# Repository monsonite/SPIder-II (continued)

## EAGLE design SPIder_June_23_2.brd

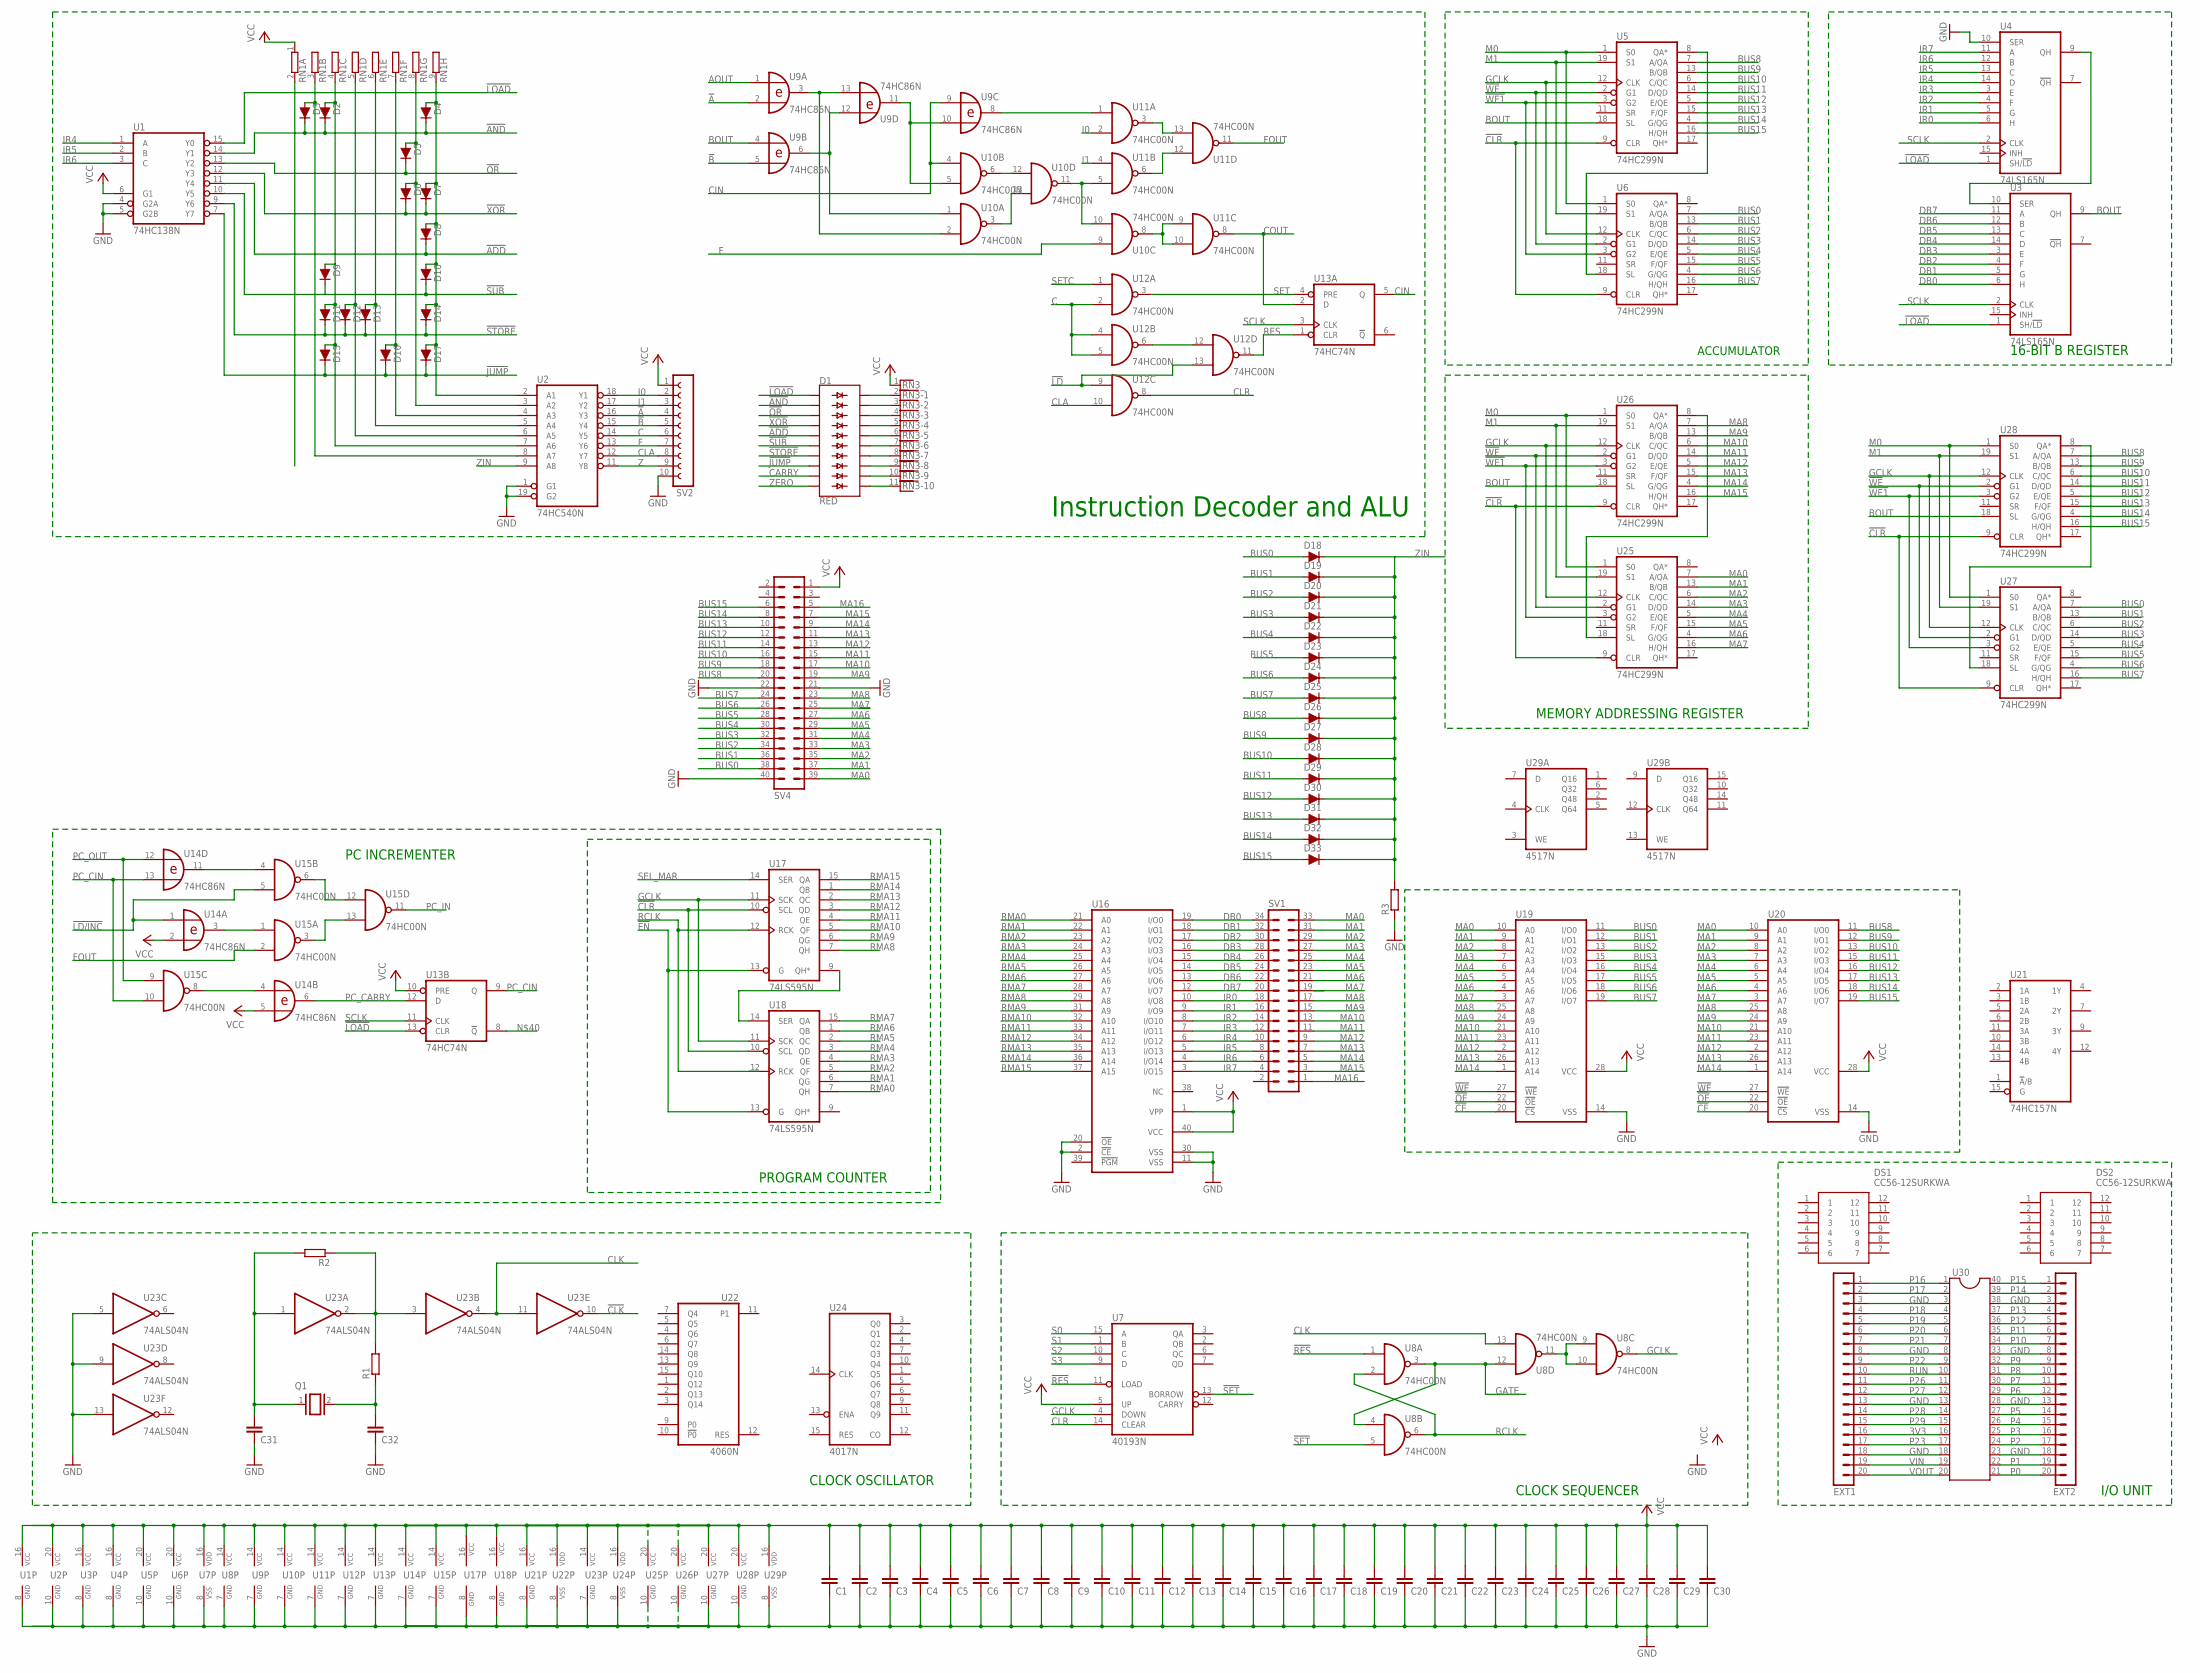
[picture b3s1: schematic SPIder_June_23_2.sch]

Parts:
C1, C2, C3, C4, C5, C6, C7, C8, C9, C10, C11, C12, C13, C14, C15, C16, C17, C18, C19, C20, C21, C22, C23, C24, C25, C26, C27, C28, C29, C30, C31, C32: C-EU025-024X044; C025-024X044
D1: RED; LED_BARGRAPH_10
D2, D3, D4, D5, D6, D7, D8, D9, D10, D11, D12, D13, D14, D15, D16, D17, D19, D20, D21, D22, D23, D24, D25, D26, D27, D28, D29, D30, D31, D32, D33: 200mA/100V/1V; DIODE-1N4148
D18: 200mA/100V/1V; DIODE-1N4148-KIT
DS1, DS2: CC56-12SURKWA; DIPS1524W75P254L5030H810Q12N
EXT1, EXT2: MA20-1
Q1: XTAL/S; QS
R1, R2, R3: R-EU_0204/5; 0204/5
RN1: GE08R; SIL9
RN3: RNX10; RN-11
SV1: MA17-2
SV2: FE10-1; FE10
SV4: MA20-2
U1: 74HC138N; DIL16
U2: 74HC540N; DIL20
U3, U4: 74LS165N; DIL16
U5, U6, U25, U26, U27, U28: 74HC299N; DIL20
U7: 40193N; DIL16
U8, U10, U11, U12, U15: 74HC00N; DIL14
U9, U14: 74HC86N; DIL14
U13: 74HC74N; DIL14
U16: 27C1024HG; DIL40
U17, U18: 74LS595N; DIL16
U19, U20: 62256P; DIL28-6
U21: 74HC157N; DIL16
U22: 4060N; DIL16
U23: 74ALS04N; DIL14
U24: 4017N; DIL16
U29: 4517N; DIL16
U30: DIL40

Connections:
3V3: EXT1.16, U30.16
!A: SV2.4, U2.16 (Y3), U9.2 (I1)
!ADD: D1.5 (A4), D8.C, U1.11 (Y4)
!AND: D1.2 (A1), D2.C, D3.C, D4.C, U1.14 (Y1)
!B: SV2.5, U2.15 (Y4), U9.5 (I1)
!CE: U19.20 (!CS), U20.20 (!CS)
!CLK: U23.10 (O)
!CLR: U5.9 (CLR), U6.9 (CLR), U17.10 (SCL), U18.10 (SCL), U25.9 (CLR), U26.9 (CLR), U27.9 (CLR), U28.9 (CLR)
!EN: U17.13 (G), U18.13 (G)
!JUMP: D1.8 (A7), D15.C, D16.C, D17.C, U1.7 (Y7)
!LD: U12.9 (I0), U12.13 (I1)
!LD/INC: U14.1 (I0), U15.5 (I1)
!LOAD: D1.1 (A), U1.15 (Y0), U3.1 (SH/!LD), U4.1 (SH/!LD), U13.13 (CLR)
!OE: U19.22 (!OE), U20.22 (!OE)
!OR: D1.3 (A2), D5.C, U1.13 (Y2)
!RES: U7.11 (LOAD), U8.1 (I0)
!SET: U7.13 (BORROW), U8.5 (I1)
!STORE: D1.7 (A6), D11.C, D12.C, D13.C, D14.C, U1.9 (Y6)
!SUB: D1.6 (A5), D9.C, D10.C, U1.10 (Y5)
!WE: U5.2 (G1), U6.2 (G1), U19.27 (!WE), U20.27 (!WE), U25.2 (G1), U26.2 (G1), U27.2 (G1), U28.2 (G1)
!WE1: U5.3 (G2), U6.3 (G2), U25.3 (G2), U26.3 (G2), U27.3 (G2), U28.3 (G2)
!XOR: D1.4 (A3), D6.C, D7.C, U1.12 (Y3)
AOUT: U9.1 (I0)
BOUT: U3.9 (QH), U5.18 (SL), U9.4 (I0), U26.18 (SL), U28.18 (SL)
BUS0: D18.A, SV4.38, U6.7 (A/QA), U19.11 (I/O0), U27.7 (A/QA)
BUS1: D19.A, SV4.36, U6.13 (B/QB), U19.12 (I/O1), U27.13 (B/QB)
BUS2: D20.A, SV4.34, U6.6 (C/QC), U19.13 (I/O2), U27.6 (C/QC)
BUS3: D21.A, SV4.32, U6.14 (D/QD), U19.15 (I/O3), U27.14 (D/QD)
BUS4: D22.A, SV4.30, U6.5 (E/QE), U19.16 (I/O4), U27.5 (E/QE)
BUS5: D23.A, SV4.28, U6.15 (F/QF), U19.17 (I/O5), U27.15 (F/QF)
BUS6: D24.A, SV4.26, U6.4 (G/QG), U19.18 (I/O6), U27.4 (G/QG)
BUS7: D25.A, SV4.24, U6.16 (H/QH), U19.19 (I/O7), U27.16 (H/QH)
BUS8: D26.A, SV4.20, U5.7 (A/QA), U20.11 (I/O0), U28.7 (A/QA)
BUS9: D27.A, SV4.18, U5.13 (B/QB), U20.12 (I/O1), U28.13 (B/QB)
BUS10: D28.A, SV4.16, U5.6 (C/QC), U20.13 (I/O2), U28.6 (C/QC)
BUS11: D29.A, SV4.14, U5.14 (D/QD), U20.15 (I/O3), U28.14 (D/QD)
BUS12: D30.A, SV4.12, U5.5 (E/QE), U20.16 (I/O4), U28.5 (E/QE)
BUS13: D31.A, SV4.10, U5.15 (F/QF), U20.17 (I/O5), U28.15 (F/QF)
BUS14: D32.A, SV4.8, U5.4 (G/QG), U20.18 (I/O6), U28.4 (G/QG)
BUS15: D33.A, SV4.6, U5.16 (H/QH), U20.19 (I/O7), U28.16 (H/QH)
C: SV2.6, U2.14 (Y5), U12.2 (I1), U12.4 (I0), U12.5 (I1)
CARRY: D1.9 (A8)
CIN: U9.9 (I0), U10.4 (I0), U13.5 (Q)
CLA: SV2.8, U2.12 (Y7), U12.10 (I1)
CLK: U8.13 (I1), U23.4 (O), U23.11 (I)
CLR: U7.14 (CLEAR), U12.8 (O)
COUT: U11.8 (O), U13.2 (D)
DB0: SV1.34, U3.6 (H), U16.19 (I/O0)
DB1: SV1.32, U3.5 (G), U16.18 (I/O1)
DB2: SV1.30, U3.4 (F), U16.17 (I/O2)
DB3: SV1.28, U3.3 (E), U16.16 (I/O3)
DB4: SV1.26, U3.14 (D), U16.15 (I/O4)
DB5: SV1.24, U3.13 (C), U16.14 (I/O5)
DB6: SV1.22, U3.12 (B), U16.13 (I/O6)
DB7: SV1.20, U3.11 (A), U16.12 (I/O7)
F: SV2.7, U2.13 (Y6), U10.9 (I0)
FOUT: U11.11 (O), U15.2 (I1)
GATE: U8.3 (O), U8.4 (I0), U8.12 (I0)
GCLK: U5.12 (CLK), U6.12 (CLK), U7.4 (DOWN), U8.8 (O), U17.11 (SCK), U18.11 (SCK), U25.12 (CLK), U26.12 (CLK), U27.12 (CLK), U28.12 (CLK)
GND: C1.1, C2.1, C3.1, C4.1, C5.1, C6.1, C7.1, C8.1, C9.1, C10.1, C11.1, C12.1, C13.1, C14.1, C15.1, C16.1, C17.1, C18.1, C19.1, C20.1, C21.1, C22.1, C23.1, C24.1, C25.1, C26.1, C27.1, C28.1, C29.1, C30.1, C31.1, C32.1, EXT1.3, EXT1.8, EXT1.13, EXT1.18, EXT2.3, EXT2.8, EXT2.13, EXT2.18, R3.1, SV2.10, SV4.21, SV4.22, SV4.40, U1.4 (G2A), U1.5 (G2B), U1.8 (GND), U2.1 (G1), U2.10 (GND), U2.19 (G2), U3.8 (GND), U4.8 (GND), U5.10 (GND), U6.10 (GND), U7.8 (VSS), U8.7 (GND), U9.7 (GND), U10.7 (GND), U11.7 (GND), U12.7 (GND), U13.7 (GND), U14.7 (GND), U15.7 (GND), U16.2 (!CE), U16.11 (VSS), U16.20 (!OE), U16.30 (VSS), U17.8 (GND), U18.8 (GND), U19.14 (VSS), U20.14 (VSS), U21.8 (GND), U22.8 (VSS), U23.5 (I), U23.7 (GND), U23.9 (I), U23.13 (I), U24.8 (VSS), U25.10 (GND), U26.10 (GND), U27.10 (GND), U28.10 (GND), U29.8 (VSS), U30.3, U30.8, U30.13, U30.18, U30.23, U30.28, U30.33, U30.38
I0: SV2.2, U2.18 (Y1), U11.2 (I1)
I1: SV2.3, U2.17 (Y2), U11.4 (I0)
IR0: SV1.18, U4.6 (H), U16.10 (I/O8)
IR1: SV1.16, U4.5 (G), U16.9 (I/O9)
IR2: SV1.14, U4.4 (F), U16.8 (I/O10)
IR3: SV1.12, U4.3 (E), U16.7 (I/O11)
IR4: SV1.10, U1.1 (A), U4.14 (D), U16.6 (I/O12)
IR5: SV1.8, U1.2 (B), U4.13 (C), U16.5 (I/O13)
IR6: SV1.6, U1.3 (C), U4.12 (B), U16.4 (I/O14)
IR7: SV1.4, U4.11 (A), U16.3 (I/O15)
M0: U5.1 (S0), U6.1 (S0), U25.1 (S0), U26.1 (S0), U27.1 (S0), U28.1 (S0)
M1: U5.19 (S1), U6.19 (S1), U25.19 (S1), U26.19 (S1), U27.19 (S1), U28.19 (S1)
MA0: SV1.33, SV4.39, U19.10 (A0), U20.10 (A0), U25.7 (A/QA)
MA1: SV1.31, SV4.37, U19.9 (A1), U20.9 (A1), U25.13 (B/QB)
MA2: SV1.29, SV4.35, U19.8 (A2), U20.8 (A2), U25.6 (C/QC)
MA3: SV1.27, SV4.33, U19.7 (A3), U20.7 (A3), U25.14 (D/QD)
MA4: SV1.25, SV4.31, U19.6 (A4), U20.6 (A4), U25.5 (E/QE)
MA5: SV1.23, SV4.29, U19.5 (A5), U20.5 (A5), U25.15 (F/QF)
MA6: SV1.21, SV4.27, U19.4 (A6), U20.4 (A6), U25.4 (G/QG)
MA7: SV1.19, SV4.25, U19.3 (A7), U20.3 (A7), U25.16 (H/QH)
MA8: SV1.17, SV4.23, U19.25 (A8), U20.25 (A8), U26.7 (A/QA)
MA9: SV1.15, SV4.19, U19.24 (A9), U20.24 (A9), U26.13 (B/QB)
MA10: SV1.13, SV4.17, U19.21 (A10), U20.21 (A10), U26.6 (C/QC)
MA11: SV1.11, SV4.15, U19.23 (A11), U20.23 (A11), U26.14 (D/QD)
MA12: SV1.9, SV4.13, U19.2 (A12), U20.2 (A12), U26.5 (E/QE)
MA13: SV1.7, SV4.11, U19.26 (A13), U20.26 (A13), U26.15 (F/QF)
MA14: SV1.5, SV4.9, U19.1 (A14), U20.1 (A14), U26.4 (G/QG)
MA15: SV1.3, SV4.7, U26.16 (H/QH)
MA16: SV1.1, SV4.5
unnamed: U3.10 (SER), U4.9 (QH)
unnamed: U17.9 (QH*), U18.14 (SER)
unnamed: U10.8 (O), U11.9 (I0), U11.10 (I1)
unnamed: U12.6 (O), U12.12 (I0)
unnamed: U25.18 (SL), U26.8 (QA*)
unnamed: U8.9 (I0), U8.10 (I1), U8.11 (O)
unnamed: U9.3 (O), U9.13 (I1), U10.2 (I1)
unnamed: U9.6 (O), U9.12 (I0), U10.1 (I0)
unnamed: U9.10 (I1), U9.11 (O), U10.5 (I1)
unnamed: U10.6 (O), U10.12 (I0)
unnamed: U10.3 (O), U10.13 (I1)
unnamed: U10.10 (I1), U10.11 (O), U11.5 (I1)
unnamed: U11.3 (O), U11.13 (I1)
unnamed: U11.6 (O), U11.12 (I0)
unnamed: U9.8 (O), U11.1 (I0)
unnamed: U27.18 (SL), U28.8 (QA*)
unnamed: D3.A, RN1.3 (2), U2.8 (A7)
unnamed: D2.A, D9.A, D11.A, D15.A, RN1.4 (2), U2.7 (A6)
unnamed: U5.8 (QA*), U6.18 (SL)
unnamed: D12.A, RN1.5 (2), U2.6 (A5)
unnamed: D1.20 (C), RN3.2
unnamed: D1.19 (C1), RN3.3
unnamed: U15.3 (O), U15.13 (I1)
unnamed: U15.6 (O), U15.12 (I0)
unnamed: D13.A, RN1.6 (2), U2.5 (A4)
unnamed: U14.11 (O), U15.4 (I0)
unnamed: U14.4 (I0), U15.8 (O)
unnamed: C31.2, Q1.1, R2.2, U23.1 (I)
unnamed: C32.2, Q1.2, R1.1
unnamed: U14.3 (O), U15.1 (I0)
unnamed: R1.2, R2.1, U23.2 (O), U23.3 (I)
unnamed: D16.A, RN1.7 (2), U2.4 (A3)
unnamed: D1.18 (C2), RN3.4
unnamed: D1.17 (C3), RN3.5
unnamed: D1.16 (C4), RN3.6
unnamed: D1.15 (C5), RN3.7
unnamed: D1.14 (C6), RN3.8
unnamed: D1.13 (C7), RN3.9
unnamed: D1.12 (C8), RN3.10
unnamed: D1.11 (C9), RN3.11
unnamed: D5.A, D6.A, RN1.8 (2), U2.3 (A2)
unnamed: D4.A, D7.A, D8.A, D10.A, D14.A, D17.A, RN1.9 (2), U2.2 (A1)
P0: EXT2.20, U30.21
P1: EXT2.19, U30.22
P2: EXT2.17, U30.24
P3: EXT2.16, U30.25
P4: EXT2.15, U30.26
P5: EXT2.14, U30.27
P6: EXT2.12, U30.29
P7: EXT2.11, U30.30
P8: EXT2.10, U30.31
P9: EXT2.9, U30.32
P10: EXT2.7, U30.34
P11: EXT2.6, U30.35
P12: EXT2.5, U30.36
P13: EXT2.4, U30.37
P14: EXT2.2, U30.39
P15: EXT2.1, U30.40
P16: EXT1.1, U30.1
P17: EXT1.2, U30.2
P18: EXT1.4, U30.4
P19: EXT1.5, U30.5
P20: EXT1.6, U30.6
P21: EXT1.7, U30.7
P22: EXT1.9, U30.9
P23: EXT1.17, U30.17
P26: EXT1.11, U30.11
P27: EXT1.12, U30.12
P28: EXT1.14, U30.14
P29: EXT1.15, U30.15
PC_CARRY: U13.12 (D), U14.6 (O)
PC_CIN: U13.9 (Q), U14.13 (I1), U15.10 (I1)
PC_IN: U15.11 (O)
PC_OUT: U14.12 (I0), U15.9 (I0)
RCLK: U8.2 (I1), U8.6 (O), U17.12 (RCK), U18.12 (RCK)
RES: U12.11 (O), U13.1 (CLR)
RMA0: U16.21 (A0), U18.7 (QH)
RMA1: U16.22 (A1), U18.6 (QG)
RMA2: U16.23 (A2), U18.5 (QF)
RMA3: U16.24 (A3), U18.4 (QE)
RMA4: U16.25 (A4), U18.3 (QD)
RMA5: U16.26 (A5), U18.2 (QC)
RMA6: U16.27 (A6), U18.1 (QB)
RMA7: U16.28 (A7), U18.15 (QA)
RMA8: U16.29 (A8), U17.7 (QH)
RMA9: U16.31 (A9), U17.6 (QG)
RMA10: U16.32 (A10), U17.5 (QF)
RMA11: U16.33 (A11), U17.4 (QE)
RMA12: U16.34 (A12), U17.3 (QD)
RMA13: U16.35 (A13), U17.2 (QC)
RMA14: U16.36 (A14), U17.1 (QB)
RMA15: U16.37 (A15), U17.15 (QA)
RUN: EXT1.10, U30.10
S0: U7.15 (A)
S1: U7.1 (B)
S2: U7.10 (C)
S3: U7.9 (D)
SCLK: U3.2 (CLK), U4.2 (CLK), U13.3 (CLK), U13.11 (CLK)
SEL_MAR: U17.14 (SER)
SET: U12.3 (O), U13.4 (PRE)
SETC: U12.1 (I0)
VCC: C1.2, C2.2, C3.2, C4.2, C5.2, C6.2, C7.2, C8.2, C9.2, C10.2, C11.2, C12.2, C13.2, C14.2, C15.2, C16.2, C17.2, C18.2, C19.2, C20.2, C21.2, C22.2, C23.2, C24.2, C25.2, C26.2, C27.2, C28.2, C29.2, C30.2, RN1.1, RN3.1, SV2.1, SV4.1, U1.6 (G1), U1.16 (VCC), U2.20 (VCC), U3.16 (VCC), U4.16 (VCC), U5.20 (VCC), U6.20 (VCC), U7.5 (UP), U7.16 (VDD), U8.14 (VCC), U9.14 (VCC), U10.14 (VCC), U11.14 (VCC), U12.14 (VCC), U13.10 (PRE), U13.14 (VCC), U14.2 (I1), U14.5 (I1), U14.14 (VCC), U15.14 (VCC), U16.1 (VPP), U16.40 (VCC), U17.16 (VCC), U18.16 (VCC), U19.28 (VCC), U20.28 (VCC), U21.16 (VCC), U22.16 (VDD), U23.14 (VCC), U24.16 (VDD), U25.20 (VCC), U26.20 (VCC), U27.20 (VCC), U28.20 (VCC), U29.16 (VDD)
VIN: EXT1.19, U30.19
VOUT: EXT1.20, U30.20
Z: SV2.9, U2.11 (Y8)
ZERO: D1.10 (A9)
ZIN: D18.C, D19.C, D20.C, D21.C, D22.C, D23.C, D24.C, D25.C, D26.C, D27.C, D28.C, D29.C, D30.C, D31.C, D32.C, D33.C, R3.2, U2.9 (A8)

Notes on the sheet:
Instruction Decoder and ALU
PC INCREMENTER
CLOCK SEQUENCER
MEMORY ADDRESSING REGISTER
ACCUMULATOR
PROGRAM COUNTER
16-BIT B REGISTER
CLOCK OSCILLATOR
I/O UNIT

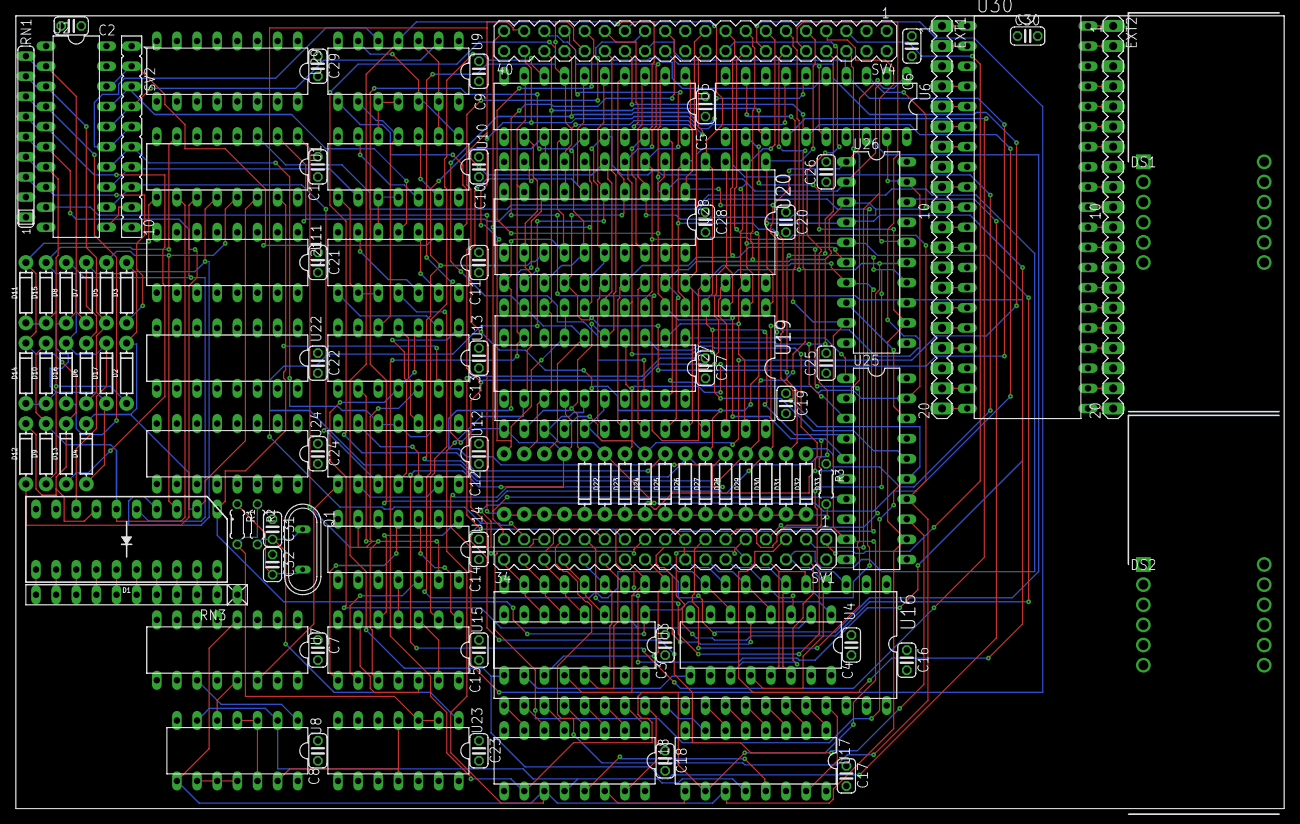
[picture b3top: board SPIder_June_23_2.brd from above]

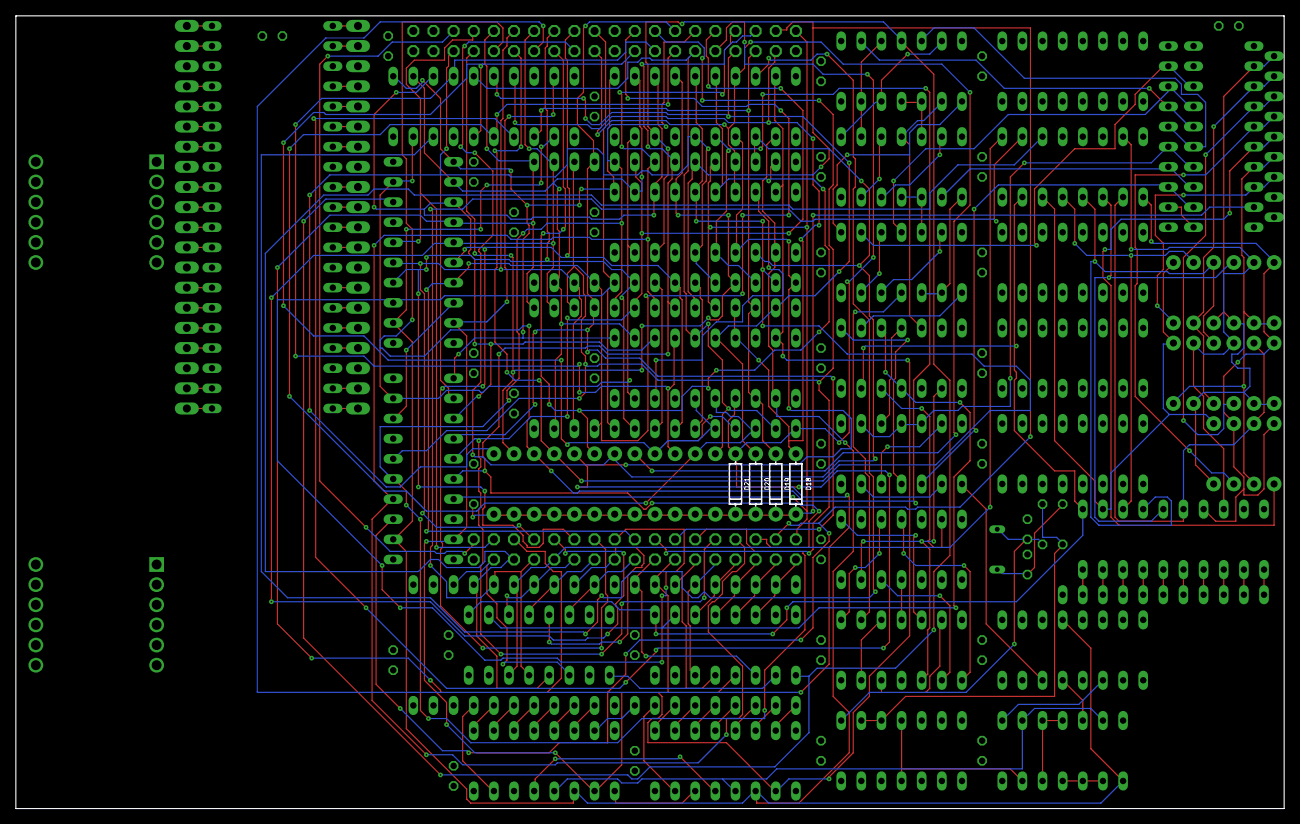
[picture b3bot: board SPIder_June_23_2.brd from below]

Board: 4 copper layers, 160.0 x 100.0 mm, 108 parts (4 on the bottom side), 185 nets.
